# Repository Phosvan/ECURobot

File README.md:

# ECUROBOT
This is the main REPO for ECURobotics. Welcome. not much here, if you are a competetor here is the sauce! Feel free to ask or send any of us an email.

We use REV sparkmax motors and drivers.

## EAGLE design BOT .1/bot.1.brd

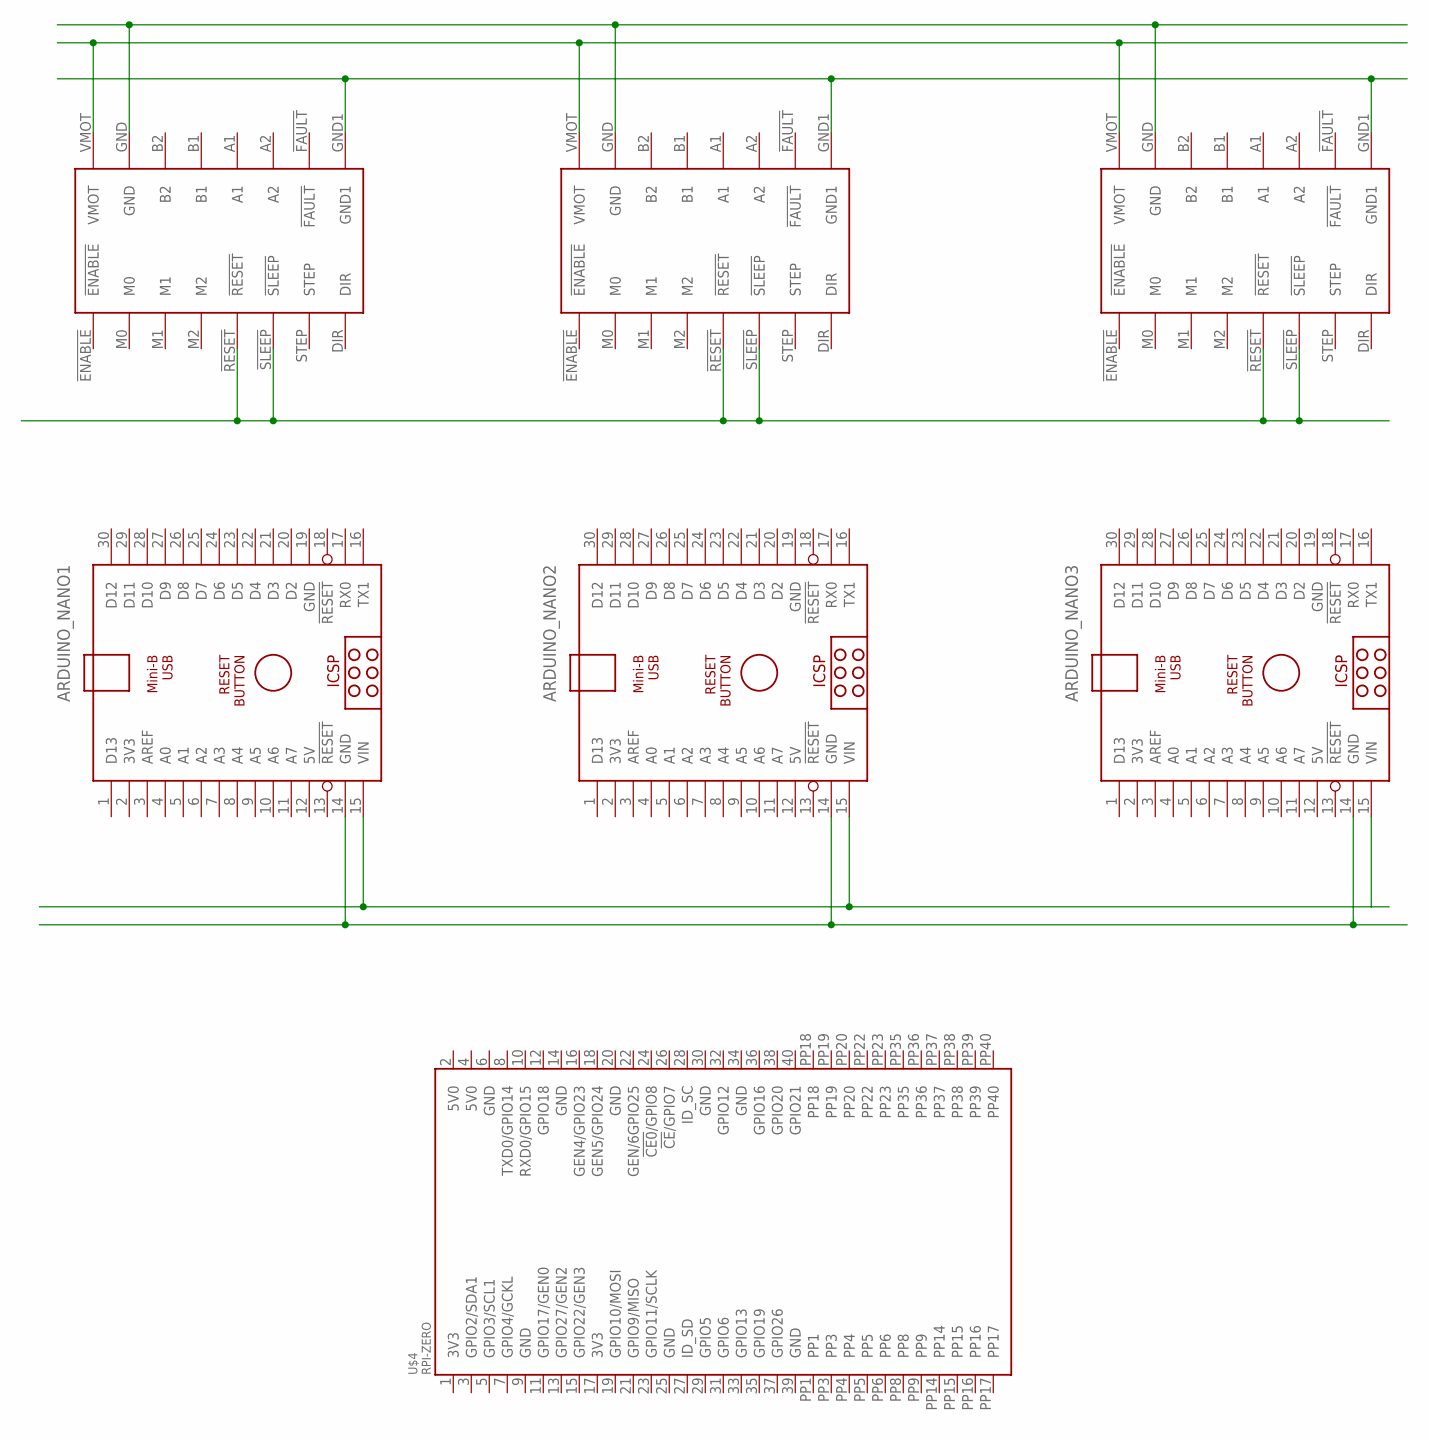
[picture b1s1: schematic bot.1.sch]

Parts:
ARDUINO_NANO1, ARDUINO_NANO2, ARDUINO_NANO3: ARDUINO_NANO
U$1, U$2, U$3: DRV8825
U$4: RPI-ZERO; RASP_PI_ZERO_BOARD_FULL

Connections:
5V: ARDUINO_NANO1.12 (5V), ARDUINO_NANO2.12 (5V), ARDUINO_NANO3.12 (5V)
GND: ARDUINO_NANO1.19 (GND), ARDUINO_NANO2.19 (GND), ARDUINO_NANO3.19 (GND)
unnamed: ARDUINO_NANO1.14 (GND), ARDUINO_NANO2.14 (GND), ARDUINO_NANO3.14 (GND)
unnamed: ARDUINO_NANO1.15 (VIN), ARDUINO_NANO2.15 (VIN), ARDUINO_NANO3.15 (VIN)
unnamed: U$1.!RESET, U$1.!SLEEP, U$2.!RESET, U$2.!SLEEP, U$3.!RESET, U$3.!SLEEP
unnamed: U$1.VMOT, U$2.VMOT, U$3.VMOT
unnamed: U$1.GND, U$2.GND, U$3.GND
unnamed: U$1.GND1, U$2.GND1, U$3.GND1

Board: 2 copper layers, 7 parts (0 on the bottom side), 8 nets, no tracks yet.

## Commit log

2021-02-25 Create Parts list per bot
2021-03-25 SP - New filesystem
2021-03-25 Revert "SP - New filesystem"
2021-03-25 Added Navi via placeholder
2021-03-25 v0.1 for Helm CLI using Curses
2021-04-03 added folders for hardware and man
2021-04-03 adding complication ;D
2021-04-03 RENAME
2021-04-03 updated sparkmaxoverUSB
